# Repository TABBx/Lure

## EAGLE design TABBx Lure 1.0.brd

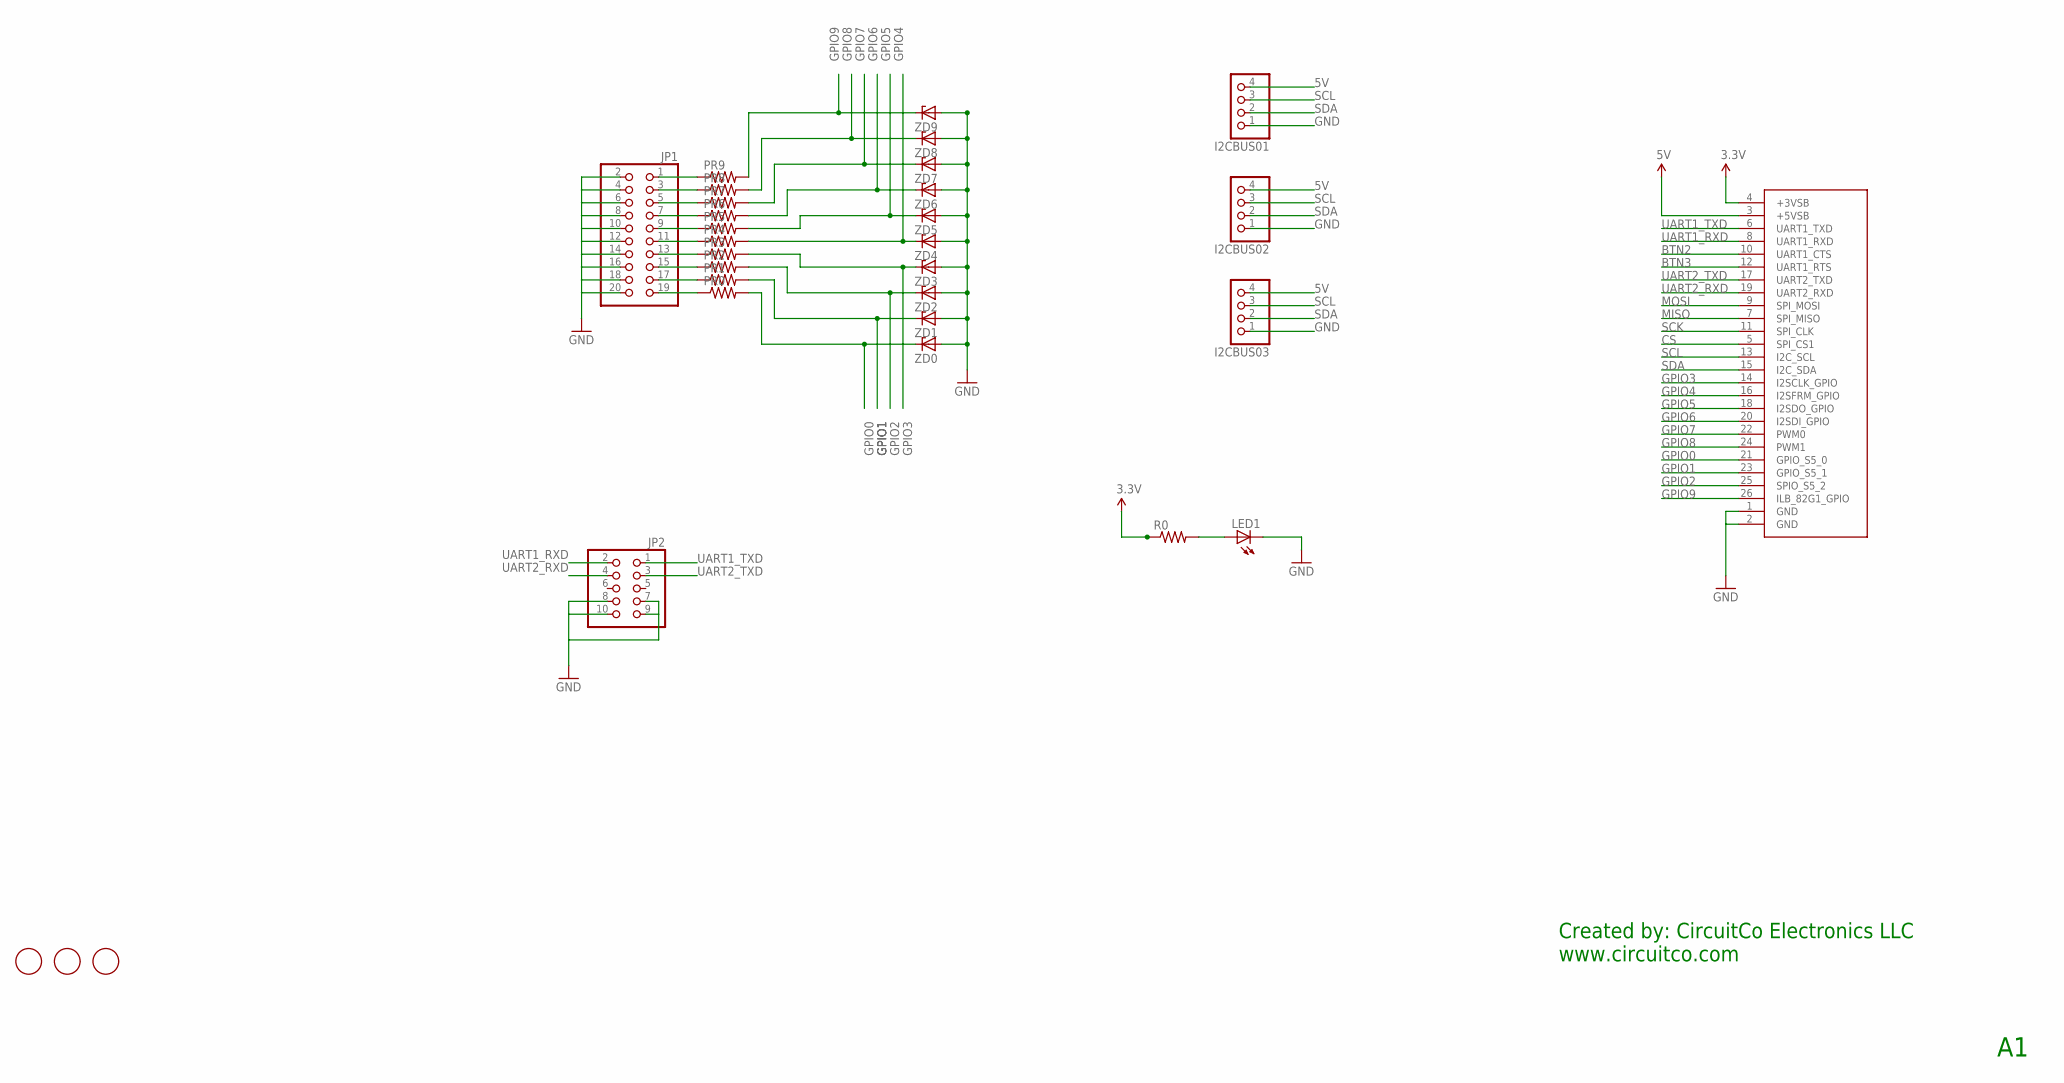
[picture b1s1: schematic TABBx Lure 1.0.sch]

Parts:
I2CBUS01, I2CBUS02, I2CBUS03: PINHD-1X4; 1X04
JP1: PINHD-2X10/90; 2X10/90
JP2: PINHD-2X5/90; 2X05/90
JP4: MINNOW2_LOW_SPEED; MINNOWBOARD_2_LOW_SPEED
LED1: LEDCHIPLED_1206; CHIPLED_1206
PR0, PR1, PR2, PR3, PR4, PR5, PR6, PR7, PR8, PR9: R-US_M1206; M1206
R0: R-US_M1206; M1206
U$3, U$5, U$6: FIDUCIAL; FIDUCIAL_1MM
ZD0, ZD1, ZD2, ZD3, ZD4, ZD5, ZD6, ZD7, ZD8, ZD9: ZENER-DIODEDO35Z10; DO35Z10

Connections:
3.3V: JP4.4 (+3VSB), R0.1
5V: I2CBUS01.4, I2CBUS02.4, I2CBUS03.4, JP4.3 (+5VSB)
BTN2: JP4.10 (UART1_CTS)
BTN3: JP4.12 (UART1_RTS)
CS: JP4.5 (SPI_CS1)
GND: I2CBUS01.1, I2CBUS02.1, I2CBUS03.1, JP1.2, JP1.4, JP1.6, JP1.8, JP1.10, JP1.12, JP1.14, JP1.16, JP1.18, JP1.20, JP2.7, JP2.8, JP2.9, JP2.10, JP4.1 (GND), JP4.2 (GND), LED1.C, ZD0.A, ZD1.A, ZD2.A, ZD3.A, ZD4.A, ZD5.A, ZD6.A, ZD7.A, ZD8.A, ZD9.A
GPIO0: JP4.21 (GPIO_S5_0), PR0.2, ZD0.C
GPIO1: JP4.23 (GPIO_S5_1), PR1.2, ZD1.C
GPIO2: JP4.25 (SPIO_S5_2), PR2.2, ZD2.C
GPIO3: JP4.14 (I2SCLK_GPIO), PR3.2, ZD3.C
GPIO4: JP4.16 (I2SFRM_GPIO), PR4.2, ZD4.C
GPIO5: JP4.18 (I2SDO_GPIO), PR5.2, ZD5.C
GPIO6: JP4.20 (I2SDI_GPIO), PR6.2, ZD6.C
GPIO7: JP4.22 (PWM0), PR7.2, ZD7.C
GPIO8: JP4.24 (PWM1), PR8.2, ZD8.C
GPIO9: JP4.26 (ILB_82G1_GPIO), PR9.2, ZD9.C
MISO: JP4.7 (SPI_MISO)
MOSI: JP4.9 (SPI_MOSI)
unnamed: JP1.1, PR9.1
unnamed: JP1.3, PR8.1
unnamed: JP1.5, PR7.1
unnamed: JP1.7, PR6.1
unnamed: JP1.9, PR5.1
unnamed: JP1.11, PR4.1
unnamed: JP1.13, PR3.1
unnamed: JP1.15, PR2.1
unnamed: JP1.17, PR1.1
unnamed: JP1.19, PR0.1
unnamed: LED1.A, R0.2
SCK: JP4.11 (SPI_CLK)
SCL: I2CBUS01.3, I2CBUS02.3, I2CBUS03.3, JP4.13 (I2C_SCL)
SDA: I2CBUS01.2, I2CBUS02.2, I2CBUS03.2, JP4.15 (I2C_SDA)
UART1_RXD: JP2.2, JP4.8 (UART1_RXD)
UART1_TXD: JP2.1, JP4.6 (UART1_TXD)
UART2_RXD: JP2.4, JP4.19 (UART2_RXD)
UART2_TXD: JP2.3, JP4.17 (UART2_TXD)

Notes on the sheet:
Created by: CircuitCo Electronics LLC www.circuitco.com

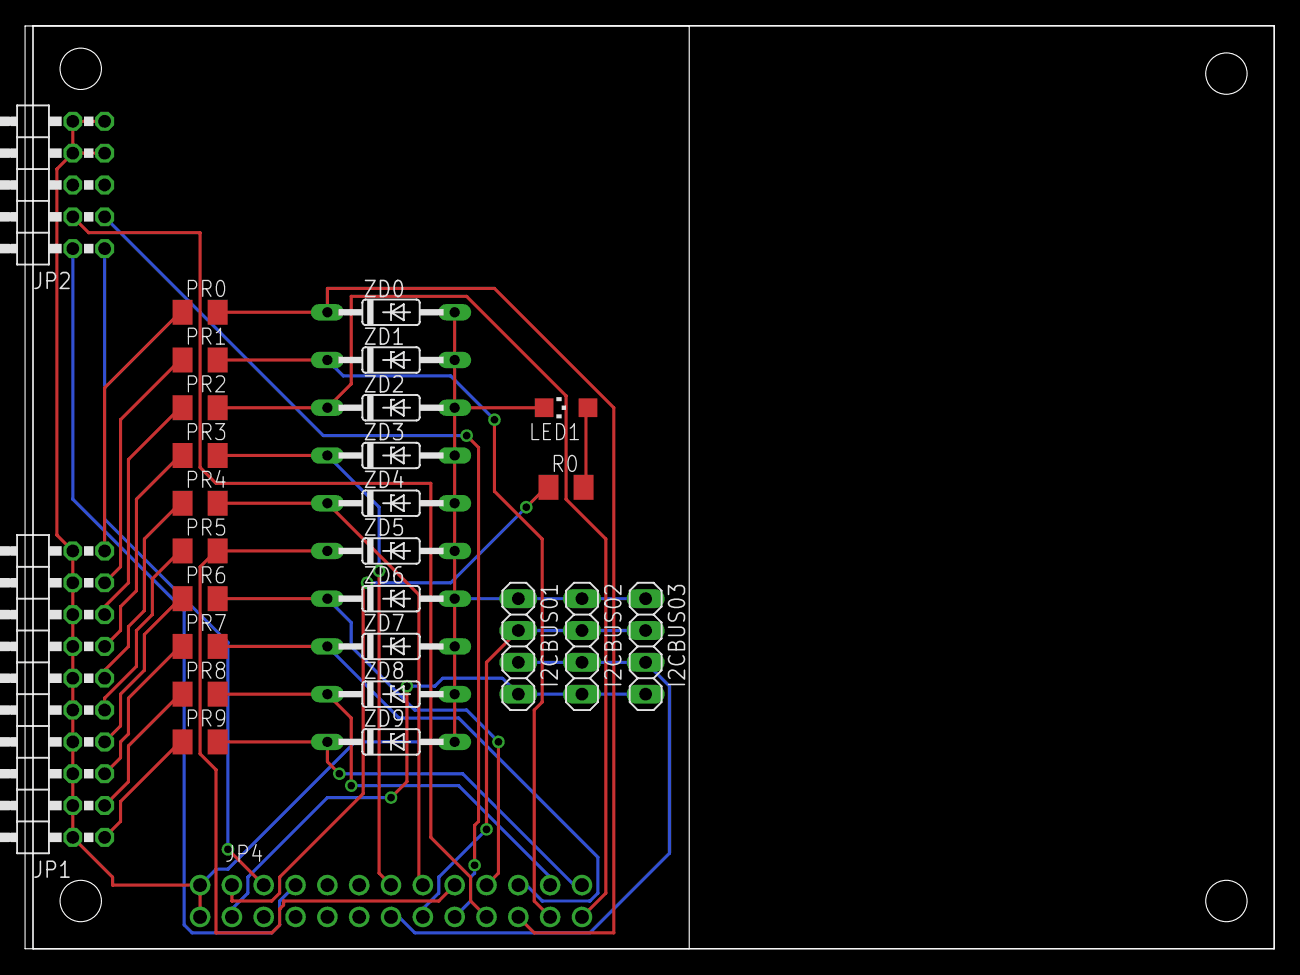
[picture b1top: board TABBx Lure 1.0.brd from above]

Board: 2 copper layers, 99.6 x 73.7 mm, 31 parts (0 on the bottom side), 30 nets.

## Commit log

2015-10-09 BRD/SCH: Initial work on TABBx lure
2015-10-12 Route, throw in a LED... everyone likes LEDs

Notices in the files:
parts and their libraries:
SparkFun-Aesthetics: Licensing: Creative Commons ShareAlike 4.0 International - https://creativecommons.org/licenses/by-sa/4.0
circuitco-creativecommons: This work is licensed under a Creative Commons
Attribution-NonCommercial 4.0 International License.
http://creativecommons.org/licenses/by-nc/4.0
